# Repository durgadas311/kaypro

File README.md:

# kaypro

Kaypro simulator and other related Kaypro items.

This repo uses submodules. After cloning, run "git submodule init".
Use "git submodule update" to refresh.

This includes the Emergency Debug Monitor, which is designed to (temporarily) replace
the system's boot ROM and allow debugging/diagnosing of issues using a serial port.
See [Emergency ROM documentation](rom/doc/monitor.pdf).
There is also a manual on [Diagnosing Kaypros](rom/doc/diags.pdf).

The simulator should not require building from source. The JAR file, and related files,
are generally available [here](http://sebhc.durgadas.com/kaypro/).

-   bin/ - contains a release version of the JAR file

-   kaypro84/ - simulator source for all Kaypro models (not just /84)

-   rom/ - Emergency Monitor ROM sourse code. for diagnosing real Kaypros, also memory test.

-   sound/ - files used to recreate Kaypro keyboard "beep"

-   configs/ - simulator config files for various models

-   disks/ - Kaypro disk images addapted for use with simulator

-   doc/ - misc info on Kaypro software/hardware

-   images/ - a collection of snapshots of my 2X and other Kaypro hardware

-   kermit/ - Kermit, with configuration for Kaypro

-   kicad/ - Schematics (ram256K modification, Kaypro-10 WD1002 interface)

-   cpm/ - CP/M 3 source code for ram256K mod

-   urom/ - copy of Kaypro UROM source code

-   util/ - works in progress

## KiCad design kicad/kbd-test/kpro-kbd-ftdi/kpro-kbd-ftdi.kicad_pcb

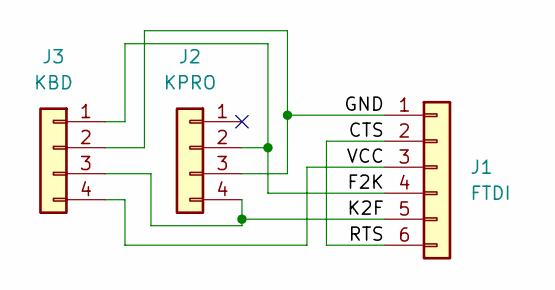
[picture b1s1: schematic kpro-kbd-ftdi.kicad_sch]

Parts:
J1: FTDI; PinHeader_1x06_P2.54mm_Vertical
J2: KPRO; PinHeader_1x04_P2.54mm_Vertical
J3: KBD; PinHeader_1x04_P2.54mm_Vertical

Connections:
/CTS: J1.2, J1.6
/F2K: J1.4, J2.2, J3.1
/GND: J1.1, J2.3, J3.2
/K2F: J1.5, J2.4, J3.3
/VCC: J1.3, J3.4

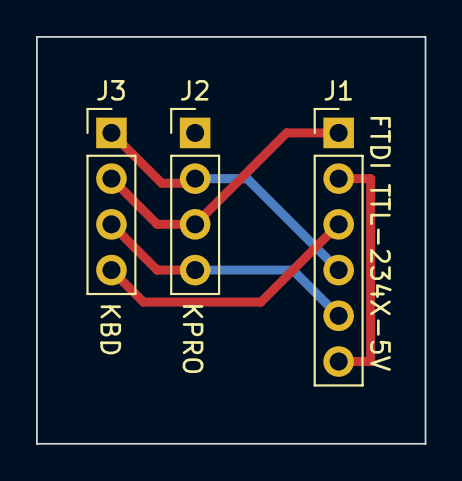
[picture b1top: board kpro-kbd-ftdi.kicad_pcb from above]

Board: 2 copper layers, 21.6 x 22.6 mm, 3 parts (0 on the bottom side), 5 nets.

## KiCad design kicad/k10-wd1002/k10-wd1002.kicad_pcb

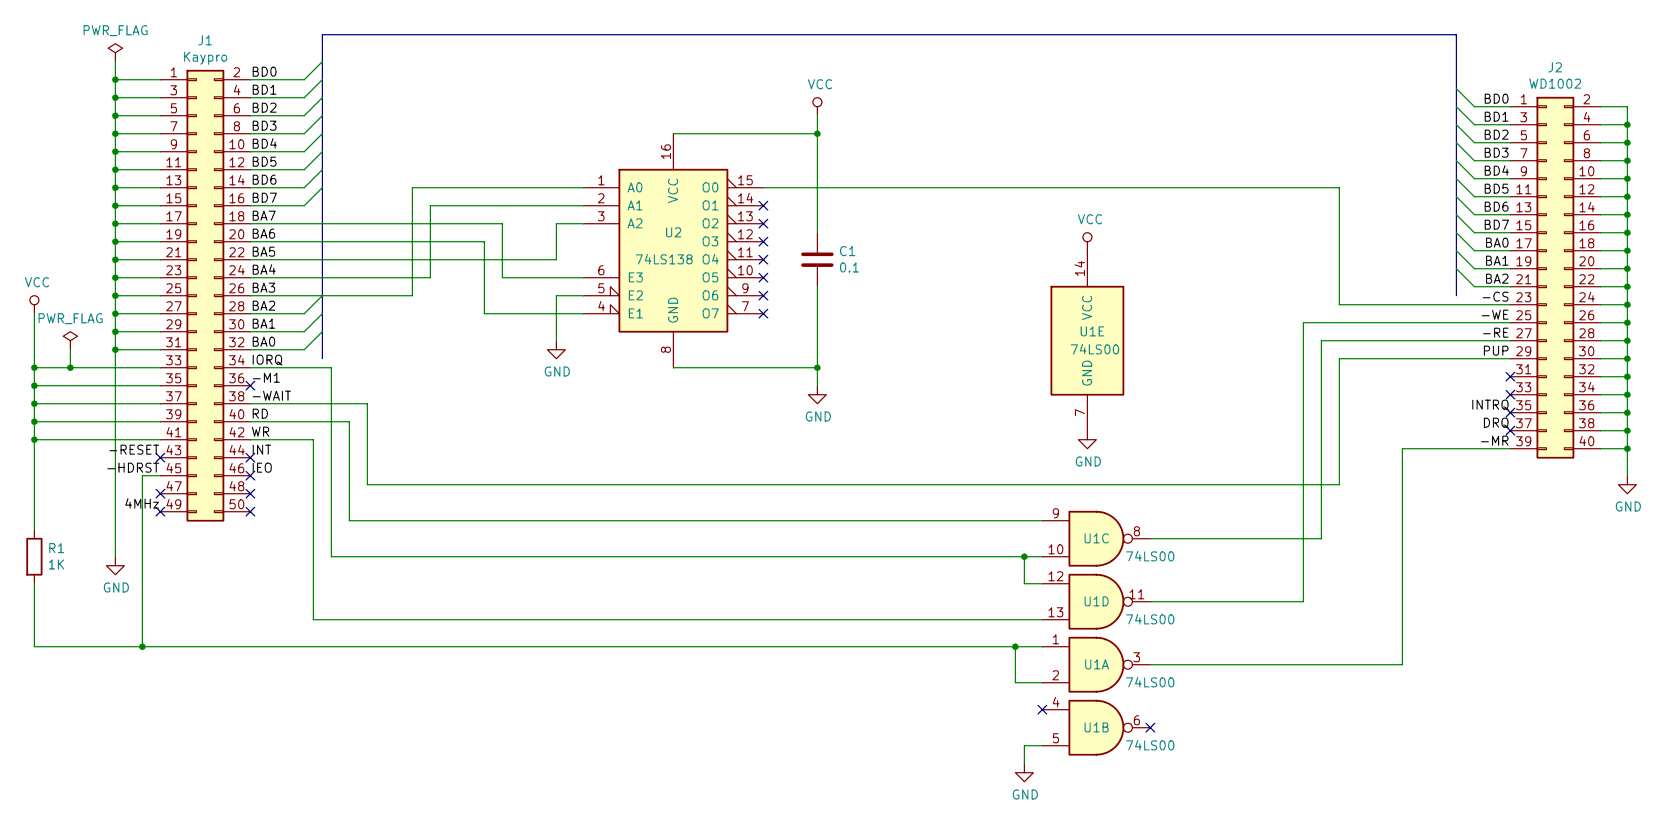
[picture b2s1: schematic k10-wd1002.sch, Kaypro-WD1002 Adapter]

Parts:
C1: 0.1
J1: Kaypro
J2: WD1002
R1: 1K
U1: 74LS00
U2: 74LS138

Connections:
/4MHz: J1.49
/-CS: J2.23, U2.15 (O0)
/-HDRST: J1.45, R1.2, U1.1, U1.2
/-M1: J1.36
/-MR: J2.39, U1.3
/-RE: J2.27, U1.8
/-RESET: J1.43
/-WAIT: J1.38, J2.29
/-WE: J2.25, U1.11
/BA0: J1.32, J2.17
/BA1: J1.30, J2.19
/BA2: J1.28, J2.21
/BA3: J1.26, U2.1 (A0)
/BA4: J1.24, U2.2 (A1)
/BA5: J1.22, U2.3 (A2)
/BA6: J1.20, U2.4 (E1)
/BA7: J1.18, U2.6 (E3)
/BD0: J1.2, J2.1
/BD1: J1.4, J2.3
/BD2: J1.6, J2.5
/BD3: J1.8, J2.7
/BD4: J1.10, J2.9
/BD5: J1.12, J2.11
/BD6: J1.14, J2.13
/BD7: J1.16, J2.15
/DRQ: J2.37
/IEO: J1.46
/INT: J1.44
/INTRQ: J2.35
/IORQ: J1.34, U1.10, U1.12
/RD: J1.40, U1.9
/WR: J1.42, U1.13
GND: C1.2, J1.1, J1.3, J1.5, J1.7, J1.9, J1.11, J1.13, J1.15, J1.17, J1.19, J1.21, J1.23, J1.25, J1.27, J1.29, J1.31, J2.2, J2.4, J2.6, J2.8, J2.10, J2.12, J2.14, J2.16, J2.18, J2.20, J2.22, J2.24, J2.26, J2.28, J2.30, J2.32, J2.34, J2.36, J2.38, J2.40, U1.5, U1.7 (GND), U2.5 (E2), U2.8 (GND)
VCC: C1.1, J1.33, J1.35, J1.37, J1.39, J1.41, R1.1, U1.14 (VCC), U2.16 (VCC)

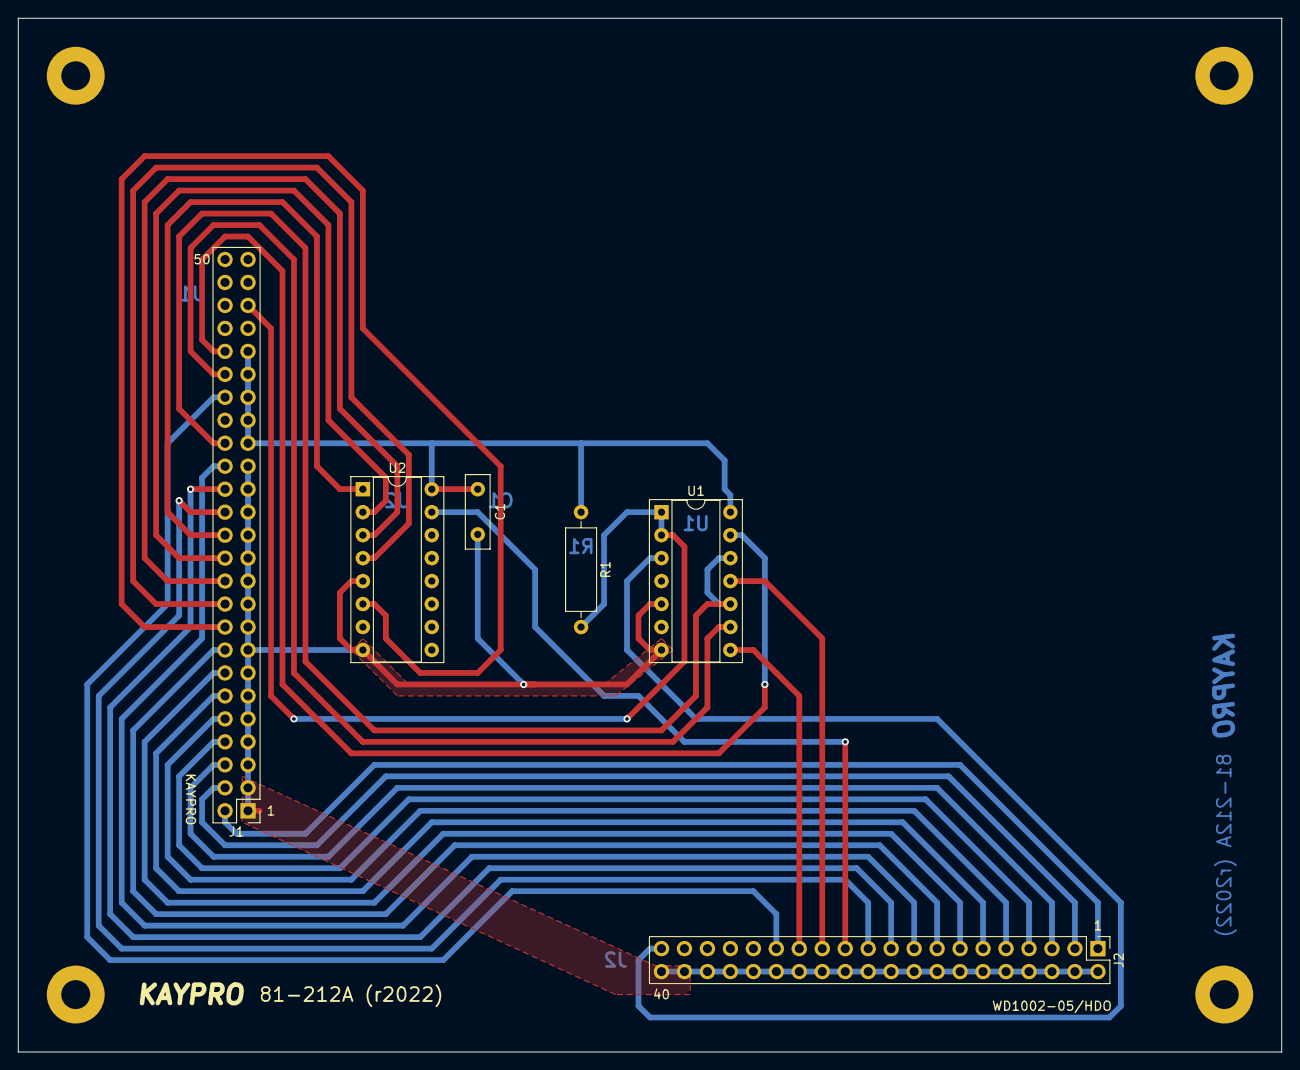
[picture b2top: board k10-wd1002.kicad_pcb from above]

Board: 2 copper layers, 139.7 x 114.3 mm, 10 parts (0 on the bottom side), 27 nets.

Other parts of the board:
 : MountingHole_3.2mm_M3_Pad
 #2,  #3,  #4: MountingHole_3.2mm_M3_Pad

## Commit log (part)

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2017-02-11 Initial pass (incomplete) at Kaypro '84 Virtual Computer
2017-02-11 Add some images and audio. First attempt at beep sound.
2017-02-11 Add some more files for Virtual Kaypro
2017-02-15 Setup attached keyboard. Prepare for Floppy+SASI Kaypro10.
2017-02-16 More work on Kaypro simulation
2017-02-17 Sketch out display RAM updates
2017-02-18 More cleanup in prep for compile
2017-02-18 Changes for compile. Add new photos.
2017-02-18 Basically functional, boots CP/M.
2017-02-19 Fix cursor on/off. Cleanup front panel.
2017-02-19 Fix a couple rough edges on screen
2017-02-19 Fix bugs handling drive names
2017-02-19 Add initial web pages
2017-02-19 Add a couple more screenshots
2017-02-19 Set aside generated tone for beep
2017-02-19 implement reverse-video cursor
2017-02-19 Save supplemental files
2017-02-19 Add some kaypro 10 diskette images
2017-02-19 Fix hang when reading sector numbers out of range. Add more diskette images.
2017-02-19 Fix disk images
2017-02-20 Add some CP/M system disk images and K10 ROM
2017-02-20 Add sample configs and blank disk. Improve device model handling.
2017-02-21 Update fonts
2017-02-24 First pass at Z80 IM2 interrupts. Fix problems with RTC. Add DRM 256K memory enhancement.
2017-02-24 Handle up to 4 drives, if no WD1002 installed.
2017-02-24 Ensure no WD1002 if 84X model
2017-02-25 Fix bug in WD1793 Type IV command status when idle
2017-02-25 Remove junk file from CP/M 3 image
2017-02-25 Add more web docs
2017-02-25 Web docs updates and prepare disk images for export
2017-02-25 Add more make targets. Add descriptions to downloads
2017-02-25 Allow front panel to display more than 2 drives
2017-02-25 Update 84X CP/M 3 screenshot
2017-02-25 Fix typo
2017-02-26 Add Kaypro 10 WD1002 winchester disk.
2017-02-27 Update harddisk images
2017-03-01 Update 84X web page
2017-03-01 Fix monitor ROM search path. Maintain Java 1.7 compatability
2017-03-01 Provide for default ROM based on machine model.
2017-03-01 Add minimal screen dump
2017-03-02 Fix problem with attributed CRT chars.
2017-03-02 Correction in model 10 hardware. Add future 10X model (CP/M 3).
2017-03-02 Update web pages for model 10
2017-03-03 Initial Z80SIO interrupt framework
2017-03-03 Typo
2017-03-03 Implement GppProvider for ParallelPrinter
2017-03-03 Get initial ParallelPrinter implementation working
2017-03-03 Use Semaphore to do true sleep in ParallelPrinter
2017-03-03 Add year to RTC regs for CP/M 3
2017-03-03 Get copy-paste working and add light-pen capability (mouse btn 3)
2017-03-03 Clear up CRT chip model
2017-03-03 Improve debug info for SY6545
2017-03-04 Try to fix bug in WD1002 - verify errors from PIP
2017-03-04 Updates for successful Kaypro 10 install
2017-03-04 Make some fixes to CP/M 3 Win modules
2017-03-05 Add model 10X config file
2017-03-05 Collect all of kaypro CP/M 3 source
2017-03-05 Minor cleanup of window title
2017-03-05 Update images and web pages.
2017-03-05 Initial import of CPNet device from Virtual H89
2017-03-05 CP/NET 3 working and shipped.
2017-03-05 Additional info for CP/NET
2017-03-05 Add note about Kaypro 10X disk B:
2017-03-05 Add screenshot of CP/NET
2017-03-05 Add link to format.jar
2017-03-05 Add link to CP/M docs
2017-03-05 Add DRI HELP files with local extensions
2017-03-05 Add mention of HELP
2017-03-06 Fix keypad encoding
2017-03-06 Gate floppy drive select with motor.
2017-03-06 Setup floppy drive timeout on init in case using HDD.
2017-03-07 Initial framework for attaching native programs to virtual I/O devices
2017-03-08 more work towards attaching process to device
2017-03-08 Add handshake/sleep to avoid overrun from peripherals
2017-03-08 Add warning about CP{/M 3 and the ROM
2017-03-08 Add Kermit-80 as downloaded.
2017-03-08 Add Kermit-80 program disk
2017-03-09 Fix bug in dir hash allocation on large drives
2017-03-09 Cleanup handling of attached/detached peripherals.
2017-03-09 Add info on winchester layouts. Add blank ST412 image for universal ROM.
2017-03-09 Add more info to ROM-CP/M matrix
2017-03-10 Update info on winchester drive formats. Add winchester image for CP/M 2.2u1.
2017-03-11 Update CP/M 3 for Universal ROM
2017-03-11 Improve Dump Page option
2017-03-11 Add Magic Wand diskette
2017-03-11 Fix a couple console problems
2017-03-11 Fix more peripheral issues.
2017-03-11 Add more supported peripherals
2017-03-11 Fix handling of paste throttle rate
2017-03-11 Make code consistent about using LUN 1. Add option to specify harddisk image file.
2017-03-11 Add CP/NET to CP/M 3 Universal ROM image
2017-03-11 Update docs
2017-03-12 Add (more-)pure CP/NET 1.2 distro image, with working SNIOS for virtual CPNetDevice.
2017-03-12 Fix hash space allocation, again. Allow for floppies to change mode.
2017-03-12 Add MODE to help and fix creation of HELP.HLP
2017-03-12 Make LDCPM3 customize LPTBL based on ROM data. Add MODE and DRIVES utils. Avoid init of WIN3KP if no drives in LPTBL.
2017-03-12 Update CP/M 3 on 81-302c image
2017-03-12 Fix some copy issues
2017-03-13 Add option to sleep and re-org menus
2017-03-13 Centralize handling of model property
2017-03-13 Drive ready includes motor status
2017-03-15 Preliminary support for QD QT drives
2017-03-15 Refactor handling of models:
    * Extend list of models
    * Change conflicting "X" for CP/M3 to be "E"
    * Allow model as commandline parameter, auto-config more.
    * More preliminary support for HD drives.
2017-03-15 Add "2X W/MODEM and CLOCK" as model "2XX"
2017-03-16 More-complete code for HiDens drives/disks
2017-03-17 Fix half-track/quarter-track media handling
2017-03-17 Add disk images for hi-density diskettes
2017-03-17 More web docs updates/cleanup
2017-03-17 Update hi-density images for latency param
2017-03-17 Add CP/M 2.2u image for hi-density drives
2017-03-18 Force disk image files to binary type
2017-03-19 Model doc update
2017-03-19 More doc updates
2017-03-19 Update MODE help
2017-03-19 Update MODE.COM in images
2017-03-19 Rotate schematic and add to web docs
2017-03-19 Update memory bank map
2017-03-21 Update schematic and include Floppy drive expansion
2017-03-23 Add basic online help
2017-03-23 Expand help and support intra-help hyperlinks
2017-03-24 Fix resize of help window and add more text
2017-03-24 Implement "About" option in Help menu
2017-03-24 Create GenericHelp widget for navigable help files
2017-09-29 Fix a couple bugs
2017-11-02 Add missed copyrights
2017-11-03 Add LICENSE
2018-01-13 Fix bug in SIO interrupt handlling
2018-01-24 Fix bug in SIO interrupt vector, fix debug dialogs to allow ENTER to accept.
2018-01-27 Fix Z80-SIO getModem() routine
2018-10-13 Fix bug in screen copy select
2018-12-02 Sync-up HostFileBdos.java with latest version for direct-use
2019-01-23 Unified VirtualUART interface
2019-06-21 Align CP/NET code with others.
2019-09-26 Fix port conflict for CP/NET virtual device, update CP/NET distros
2019-09-26 Update web page info for CP/NET
2019-09-28 Add ability to disable SYS attribute in HostFileBdos, for use on Windows
2019-12-10 Mention DazzleStar TNG
2020-01-22 Fix bug in Z80-SIO status-affects-vector handling
2020-05-24 Align HostFileBdos, et al., code with mainstream
2020-07-03 Add core dump command for debugging.
2020-07-07 PRELIMINARY support for Kaypro II et al.
2020-07-08 Remove deprecated interfaces from VirtualPPort
2020-07-08 Fix Kaypro II font geometry
2020-07-12 Use active SerialDevice interface for serial output, add TtySerial and TelnetSerial
2020-07-18 Fix problemns with Z80-SIO ports on CP/M 3
2020-07-18 Add some SerialDevice debug, fix Z80-SIO early setModem() calls.
2020-07-19 Implement latched CTS/DCD, Ch A Intr Pending bit.
2020-07-20 Add UROM source code, initial build with M80/L80
2020-07-20 Reset UROM code back to 81-478a, v2.01
2020-07-20 Update UROM code to v2.02 (81-478b)
2020-07-20 Update docs on new urom versions
2020-07-21 Make LDCPM3 compatible with 81-478 ROMs > 2.01
2020-07-26 Align Kaypro CP/M 3 BIOS interfaces with MMS H89.
2021-02-12 Silence debug message in ProgramSerial
2021-04-17 Change location for www files
2021-05-23 Add Magic Wand documentation
2022-03-16 Add more K10-WD1002 adapter images
2022-03-16 Add schematic for K10-WD1002 adapter board
2022-03-17 Revise and correct K10-WD1002 schematic
2022-03-18 Refine K10-WD1002 PCB layout
2022-03-19 Finish PCB layout
2022-03-23 Fix mounting holes and cleanup GND zones
2022-05-04 Add Kaypro IV mainboard photo (lkramer)
2022-12-10 Syncup HostFileBdos.java with VirtualCpm version (fix SEARCH)
2023-01-21 Convert to using z80debug for tracing/disassembling
2023-05-14 Add debug monitor ROM
2023-05-15 Add monitor doc and tweak monitor
2023-05-17 Add */83 heartbeat
2023-05-18 Add memtest ROM image and document it
2023-05-18 monitor: Keep floppy motor off
2023-05-19 monitor: add h/w assist commands
2023-05-20 Fix CRTC handling of update bit
2023-05-20 Fix CRTC test of update bit
2023-05-20 monitor: add keyboard test
2023-05-20 monitor: turn off heartbeat and add extract command
2023-05-20 Fixup .htaccess
2023-05-21 monitor: add feedback for GO command
2023-05-22 split rom build for 2716 (Kaypro-II early models)
2023-05-22 Fix hard-coded clockspeed in floppy, affecting index pulse timing
2023-05-23 monitor: doc cleanup
2023-05-23 monitor: fix init of RTS
2023-05-23 Add VRT test
2023-05-24 monitor: add CRTC register test
2023-05-24 add framework for injecting errors for CRTC register test
2023-05-25 Make parallel printer mimic status when not connected
2023-05-25 monitor: add floppy read command
2023-05-25 Make memtest use serial port
2023-05-27 Handle self-test command, incl. at RESET
2023-05-27 Add HDD init/test commands
2023-05-27 add RS232 adapter pinout
2023-05-29 monitor: add info on disk layouts
2023-05-29 Add github README
2023-05-29 monitor: cleanup doc and fix typos
2023-06-02 monitor: fix T CRTC
2023-06-02 monitor: add help for connecting serial port
2023-06-03 notify PIO listener when mode 3 is set
2023-06-04 First pass at diagnostic manual
2023-06-04 monitor: add HDD details
2023-06-08 monitor: update docs, add more kbd testing options
2023-06-10 generalize sample gathering and define entry points
2023-06-11 monitor: add Hexload command
2023-06-11 monitor: fix typos in diags.pdf
2023-06-15 add more images
2023-06-16 add Kaypro Keyboard app
2023-06-16 add pics of keyboard
2023-06-17 monitor: add vkbd files
2023-06-20 monitor: clarifications in diags doc
2023-08-21 Fix problem with RTC chip in different Locales.
    I've tried to run VirtualKaypro.jar on Windows 10 with Polish language
    and locale, but it crashed. When changed date format to United States
    it works ok. Problem lies in parsing of the date time string.
    Fix is simple: in MM58167.java add:
    import java.util.Locale;
    And modify:
2023-09-24 Add initial work on KayNet/WEB-NT PCB
2023-12-10 Update schematics etc for WEB-NT product
2023-12-10 initial disassembly of WEB-NT OS components
2023-12-10 create osovl.asm for both versions
2023-12-10 cleanup some bits in osovl.asm
2023-12-11 render web-nt-waveforms and add missing files
2023-12-12 separate clock vs. cp/m config options
2023-12-13 make generic web.asm and more disas on osovl
2023-12-17 web-nt: more analysis and disas
2025-06-05 add kaynet distro s/w
2025-06-09 add KayNetSerial device
2025-06-10 implement simpler explanation for ULCNet handshake signals
2025-06-15 working KayNetSerial, updated schematic
2025-06-15 add minimal KayNet schematic
2025-06-19 update kaynet-ulcnet schematic
2025-06-19 add ULCOPS.COM for different workstations
2025-06-19 make a release of KayNet
2026-03-07 util for mangling a ROM image on address lines
2026-03-07 more photos of mainboards
2026-03-07 refinement of KayNet ULCNET schematic
2026-05-01 Archive copy of 8-bit Kaypro imgs on https://www.mrynet.com/kaypro/software.html
2026-05-14 Use normal Z80SIO attatch path for KayproKeyboard, allowing for alt implementations
2026-05-17 add bin2hex util
2026-06-01 add wordstar 3.3 master w/acc
2026-06-03 add util for 2.2u1 keypad setup for MW
2026-06-04 add lastest jars
2026-06-04 Convert to using submodule for jserialcomm
2026-06-05 update diablo630 submodule
2026-06-10 use consistent arg processing for diablo630
